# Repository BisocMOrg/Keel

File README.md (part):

# Keel

Keel is a Raspberry Pi 4 robot baseboard with two DC motor channels, an ultrasonic sensor interface, six RGB LEDs, four illuminated buttons and I²C expansion. The Pi mounts inverted through a 40-pin socket. A hardware AND gate enables the motors only when the host requests it, the STM32C011 controller grants permission and the fault bus is clear.

The repository contains the R3 hardware design, STM32 firmware, C libraries for board control (libkeel) and camera operation (libkeel-camera), Python and Java bindings, and a 3D-printable chassis.

The R3 board has been manufactured, assembled and tested on hardware. The [verification results](#verification)
cover motor drive, the safety chain, LEDs, buttons and camera operation.

<p align="center">
  <br>
  <sub>Robot chassis design (render).</sub>
</p>

## Contents

- [Hardware](#hardware)
- [Motor enable chain](#motor-enable-chain)
- [Software](#software)
- [Demonstrators](#demonstrators)
- [Camera](#camera)
- [Robot chassis](#robot-chassis)
- [Building and installing](#building-and-installing)
- [Verification](#verification)
- [Repository layout](#repository-layout)
- [Documentation](#documentation)
- [Licences](#licences)

## Hardware

| Parameter | Value |
|---|---|
| Revision | R3 (2026-11) |
| Board | 106 x 150 mm, 6 layers, 1.6 mm, KiCad 10 |
| Host | Raspberry Pi 4, mounted upside down on a 2x20 socket (PI1) with a booster header, about 19.5 mm stack height |
| Supply | 5 V from host header pins 2 and 4, through a TVS clamp (D7) and an eFuse (U2, TPS259474L) with under- and over-voltage cut-off; over-voltage trip 5.28-5.47 V |
| Motor driver | DRV8411 dual H-bridge (U1), four host PWM lines, current regulation through 0.82 Ohm sense resistors: 0.22-0.28 A per motor |
| Motor connectors | J2 (left), J3 (right): 2-pin 1.5 mm side entry |
| Safety controller | STM32C011F4P6 (U12) on its own 3.3 V rail (U16), window watchdog TPS3436 (U13), 3-input AND gates for the motor (U14) and servo (U27) enables |
| Ultrasonic socket | J1, 4-pin 2.54 mm (5 V, TRIG, ECHO, GND) for an HC-SR04; 5 V switched by U30 (TPS2553-1), 108-154 mA limit; open-drain trigger buffer and echo buffer |
| Servo header | J5, not fitted on R3; 5 V switched by U15 (TPS2553-1), 444-568 mA limit, timed bursts only |
| LEDs | Six RGB LEDs on the bottom side, IS31FL3218 driver (U3) at I2C address 0x54, up to 6.3 mA per channel; four white LEDs at the buttons on host GPIOs |
| Buttons | SW1-SW4 (A, B, X, Y), active low on host GPIOs |
| Expansion | I2C through a repeater (U6) and an over-voltage protector (U10): two 4-pin 1.0 mm sockets (X1, X3) on a 3.3 V accessory rail (U4, LT1763), plus six unfitted header positions (J4, JP1-JP5) |
| ESD | Clamp arrays at every external connector and the buttons |
| Test access | 28 bare pads on the bottom side on a 2.54 mm grid |
| Programming | SW5 (4-pole DIP): all ON = programming (host GPIO0/1/7 connect to the controller's SWD and reset), all OFF = normal operation |

<p align="center">
  <br>
  <sub>Physical R3 board (top row) and CAD renders (bottom row); top side left, bottom side right.</sub>
</p>

### Connections

| Device | Connects to | Path |
|---|---|---|
| Raspberry Pi 4 | PI1, through a 2x20 booster header | Keel takes its 5 V from the Pi's header pins 2 and 4 and uses the GPIO lines listed below |
| Two DC gearmotors | J2 (left), J3 (right) | U1, behind the motor enable gate |
| HC-SR04 ultrasonic sensor | J1, near the front | 5 V switched and current-limited by U30; TRIG and ECHO buffered to GPIO13 and GPIO25 |
| I2C accessories | X1, X3 (pin 1 GND, pin 2 3.3 V, pin 3 SDA, pin 4 SCL) | U6 repeater and U10 over-voltage protector on I2C1 |
| Raspberry Pi Camera Module 2 or 3 | The Pi's own camera connector, with a 15-way 1.0 mm flat cable | Not through Keel |
| Power source, 5 V / 3 A | The Pi's USB-C input (the chassis uses a USB-C power bank) | Not through Keel: the board and the motors run from the Pi's 5 V |

Keel has no connection to the Pi's camera and display connectors, USB, Ethernet or HDMI, or to GPIO14 and GPIO15
(UART).

### Host GPIO assignment

| BCM | Header pin | Signal | Direction (host) | Function |
|---|---|---|---|---|
| 2, 3 | 3, 5 | I2C_SDA, I2C_SCL | bidirectional | I2C1: LED driver and expansion bus |
| 4 | 7 | I2C_INT | input | Expansion interrupt (buffered, active low) |
| 8, 11 | 24, 23 | MOTOR_LP, MOTOR_LN | output | Left motor PWM |
| 10, 9 | 19, 21 | MOTOR_RP, MOTOR_RN | output | Right motor PWM |
| 26 | 37 | MOTOR_EN | output | Motor enable request (AND gate input; also the arming handshake) |
| 18 | 12 | HOST_HEARTBEAT | output | Heartbeat to the safety controller |
| 19 | 35 | SERVO_REQUEST | output | Servo power request |
| 12 | 32 | SERVO_SIG | output | Servo signal |
| 20 | 38 | HOST_FAULT | input | READY: high while the safety controller is healthy |
| 21 | 40 | HOST_ARMED | input | ARMED: high while the motor driver is enabled |
| 13 | 33 | US_TRIG | output | Ultrasonic trigger |
| 25 | 22 | US_ECHO | input | Ultrasonic echo |
| 5, 6, 16, 24 | 29, 31, 36, 18 | SW_A, SW_B, SW_X, SW_Y | input | Buttons, active low |
| 23, 22, 17, 27 | 16, 15, 11, 13 | LED_A, LED_B, LED_X, LED_Y | output | Button LEDs |
| 0, 1, 7 | 27, 28, 26 | PI_PROG_SWDIO, PI_PROG_SWCLK, PI_PROG_NRST | - | Controller programming, connected only while SW5 is ON |
| 14, 15 | 8, 10 | - | - | Not connected |

<p align="center">
  <br>
  <sub>Schematic sheet 1 of 11 (host socket and block diagram). The full schematic is <a href="hardware/schematic/Keel_R3_schematic.pdf">Keel_R3_schematic.pdf</a>.</sub>
</p>

## Motor enable chain

```mermaid
flowchart LR
    subgraph PI["Raspberry Pi 4"]
        LIB["libkeel control loop"]
    end
    LIB -- "HOST_HEARTBEAT (GPIO18)" --> MCU["STM32C011 (U12)"]
    WD["Window watchdog (U13)"] -. "reset on missed service" .-> MCU
    LIB -- "MOTOR_EN (GPIO26)" --> AND{"AND (U14)"}
    MCU -- "MCU_MOTOR_PERMIT" --> AND
    FB["MOTOR_FAULT bus (open drain)"] --> AND
    AND -- "MOTOR_EN_SAFE = nSLEEP" --> DRV["DRV8411 (U1)"]
    LIB -- "PWM, 4 lines" --> DRV
    DRV --> MOT(("J2, J3"))
    MCU -- "READY (GPIO20)" --> LIB
    AND -- "ARMED (GPIO21)" --> LIB
```

- `nSLEEP = MOTOR_EN AND MCU_MOTOR_PERMIT AND MOTOR_FAULT`. The servo switch enable is built the same way (U27) with
  the controller's servo permit.
- The controller raises `MCU_MOTOR_PERMIT` only after an arming sequence on `MOTOR_EN` with a heartbeat inside its
  timing window, and lowers it on a missed heartbeat, a PWM edge outside the permitted states, or any latched fault.
  After a fault the host must repeat the arming sequence.
- `MOTOR_FAULT` is an open-drain bus with a 22 kOhm pull-up. It is pulled low by the 5 V supervisor (U11, below
  4.65 V), the watchdog output (U13) and the sensor and servo switches (U30, U15). A low bus disables both enables and
  resets the controller. The controller cannot drive the bus.
- U1's own nFAULT output (pin 8) is not connected: on the bus it would gate U1's own nSLEEP during its wake-up pulse.
  The DRV8411 still protects itself (over-current, thermal shutdown, under-voltage lockout).
- The disable path contains no firmware: the host or the fault bus can remove motor power alone.

Measured on hardware: `ARMED` falls 9-37 us after a host stop command, and 51-71 ms after the host process is killed
(heartbeat stops; design bound about 86 ms after the last heartbeat edge). The full host and controller contract is in
[`firmware/safety-mcu/docs/mcu_integration.md`](firmware/safety-mcu/docs/mcu_integration.md).

The board is an engineering safety interlock, not a certified safety device.

## Software

| Component | Description |
|---|---|
| [`software/libkeel`](software/libkeel/README.md) | C11 host library for the board, ABI 1.0, `libkeel.so.1`, header `keel/keel.h`. Backends: `r3` (GPIO character device, i2c-dev, real-time PWM thread) and `simulator` (steps an unmodified copy of the controller's policy code). |
| [libkeel-camera](software/libkeel/docs/camera.md) | C camera library, ABI 1.0, `libkeel-camera.so.1`, header `keel/camera.h`, in the libkeel source tree (`software/libkeel/src/camera`). See [Camera](#camera). |
| Tools | `keel-doctor` (checks device access, GPIO lines, real-time limits, I2C), `keel-live` (hardware test modes), `keel-demo`, `keel-setup` (groups and boot configuration), all in `keel-tools`; `keel-camera` (camera list, stills, recording, streaming, raw frames) in its own package. |
| Debian packages | Board: `libkeel1`, `libkeel-dev`, `keel-common`, `keel-tools`. Camera: `libkeel-camera1`, `libkeel-camera-dev`, `keel-camera`. Python binding: `python3-keel`. The board packages do not depend on the camera packages. |
| [`software/bindings/python`](software/bindings/python/README.md) | Python 3.11+ binding over ctypes, distribution `keel-robot`, import name `keel`. Packages `keel.errors`, `keel.loop`, `keel.state`, `keel.peripherals`, `keel.sim`, and `keel.camera` for the camera; `keel` re-exports every board name. |
| [`software/bindings/java`](software/bindings/java/README.md) | Java 25+ binding over the Foreign Function and Memory API, `io.github.bisocmorg:keel`, module `io.github.bisocmorg.keel`. Packages `io.github.bisocmorg.keel` and its subpackages `errors`, `loop`, `state`, `peripherals`, `sim`, and `camera` for the camera; no native code. |
| [Java and Python demonstrators](software/demonstrator/README.md) | Two independent Pi servers with a shared local browser dashboard: interactive 3D robot, LEDs, hold-to-drive motors, ultrasonic ranging, camera streaming/photos and measured timing statistics. |
| [`firmware/safety-mcu`](firmware/safety-mcu/README.md) | STM32C011 firmware, release image (`release/safety_controller.hex`, SHA-256 `1608d866...`) and the programming tool for the Pi (`programming/flash_safety_mcu.sh`). |

The low-level bindings pass calls through to libkeel. Their sequential task layer schedules bounded actions
without replacing the native safety policy. Constants and structure layouts are generated from `keel.h` and
`camera.h` and checked in CI.

Threading rule: the thread that runs the control loop owns the device. Motion calls from any other thread are refused
(`KEEL_E_CONFLICT`); stop calls (`keel_disarm`, `keel_emergency_stop`, `keel_close`) are accepted from any thread. The
GPIO lines are requested exclusively, so a second process cannot open the board (`KEEL_E_IN_USE`).

Sequential task (Python): drive both motors at 20% for 3 s, pause with motor drive off, then make a timed left turn.
The task runner handles arming, the hardware loop, bounded movement and cleanup. Students write their own
behaviours; see the [Java/Python task guide](software/bindings/docs/tasks.md).

```python
import time

import keel
from keel.task import KeelTask

class FirstTask(KeelTask):
    """Run a short sequence of bounded robot movements."""

    def run(self) -> None:
        """Drive, pause with motor drive off, then turn."""
        self.keel.drive_for(20, 20, 3000)  # percent left/right, milliseconds
        time.sleep(0.5)
        self.keel.turn_left_for(600)

keel.run(FirstTask())
```

<details>
<summary>Java</summary>

```java
import io.github.bisocmorg.keel.Keel;
import io.github.bisocmorg.keel.task.KeelTask;

public final class FirstTask extends KeelTask {
    /**
     * Runs sequential actions, each ending with zero motor drive.
     * @throws Exception if an action fails or the task is interrupted
     */
    @Override
    protected void run() throws Exception {
        keel.driveFor(20, 20, 3000);
        Thread.sleep(500);
        keel.turnLeftFor(600);
    }

    /**
     * Executes this task and closes its hardware resources.
     * @param args unused command-line arguments
     * @throws Exception if opening the robot or running the task fails
     */
    public static void main(String[] args) throws Exception {
        Keel.run(new FirstTask());
    }
}
```

`java --enable-native-access=ALL-UNNAMED -cp keel-1.0.0.jar FirstTask.java`

</details>

<details>
<summary>C</summary>

```c
#include <keel/keel.h>
#include <stdio.h>

int main(void)
{
    keel_open_report report = {.struct_size = sizeof report};
    keel_device *dev = NULL;
    int32_t rc = keel_open(NULL, &dev, &report);
    if (rc != KEEL_OK) {
        fprintf(stderr, "keel_open: %s: %s\n", keel_status_name(rc), report.hint);
        return 1;
    }

    keel_cycle_input in = {.struct_size = sizeof in, .health = KEEL_HEALTH_ALL};
    keel_snapshot out = {.struct_size = sizeof out};
    uint64_t next = 0;
    keel_now_us(dev, &next);
    rc = keel_request_arm(dev);

    for (int i = 0; rc == KEEL_OK && i < 300; ++i) {
        in.cycle_id++;
        if (out.state == KEEL_STATE_ARMED) {
            in.command = KEEL_CYCLE_DRIVE;
            in.left = 200;
            in.right = 200;
        }
        rc = keel_cycle(dev, &in, &out);
        next += 10000;
        if (rc == KEEL_OK) {
            rc = keel_sleep_until(dev, next);
        }
    }
    keel_close(dev, NULL);
    return rc == KEEL_OK ? 0 : 1;
}
```

`cc -std=c11 drive.c $(pkg-config --cflags --libs keel) -o drive`

</details>

Further examples are in [`software/bindings/python/examples`](software/bindings/python/examples) and
[`software/bindings/java/examples`](software/bindings/java/examples): buttons, LEDs, ranging, fault handling and
driving, and for the camera frames, streaming and stills.

The board examples use sequential tasks or managed `RobotSession` connections instead of constructing
hardware control loops. The browser demonstrators use managed sessions with explicit arming and finite
drive-command leases. Camera-only examples keep the high-level camera API and need no board connection.

## Demonstrators

The [Java and Python demonstrators](software/demonstrator/README.md) run on the Raspberry Pi and serve a browser
dashboard over the local network. They are independent server implementations with the same controls and shared
browser interface. Each uses its own language binding to `libkeel` and `libkeel-camera`; the browser assets and 3D
model are bundled, so the dashboard needs no internet connection.

<p align="center">
  <br>
  <sub>Shared Java/Python dashboard, shown with Python connected to the robot and motors disarmed.</sub>
</p>

| Implementation | Source | Default browser address |
|---|---|---|
| Python 3.11+ | [`software/demonstrator/python/`](software/demonstrator/python/) | `http://ROBOT:8787` |
| Java 25+ | [`software/demonstrator/java/`](software/demonstrator/java/) | `http://ROBOT:8788` |

Replace `ROBOT` with the Pi's hostname or IP address. Both provide:

- An interactive 3D model of the assembled robot, with selectable wheels, LEDs, buttons, camera and ultrasonic sensor.
- Individual RGB LEDs and button indicators, physical button readings and ultrasonic distance measurements.
- Motor arming, hold-to-drive controls, disarming and a latched emergency stop. Wheel animation shows commanded
  duty, not measured speed.
- A 640 x 480 MJPEG camera feed, full-resolution JPEG photos and autofocus on supported cameras. Taking a photo
  briefly pauses and resumes the stream.
- Network round-trip time, estimated camera-frame age with clock-sync uncertainty, delivered FPS, throughput,
  dropped/skipped frames, control-loop timing and CPU temperature when available.

Follow the [build and upload instructions](software/demonstrator/README.md#build-on-the-pc) to package both versions
and copy them to the Pi. From the extracted deployment directory:

```sh
./demo use python   # Python controls the hardware; Java runs in mock mode
./demo token        # Access token to enter in the browser
./demo use java     # Switch hardware control to Java; Python becomes mock
./demo mock         # Run both without physical hardware
./demo stop         # Stop both servers
```

Only one implementation can own the physical board and camera at a time. The browser requires explicit control
ownership and motor arming. Motor commands expire after 350 ms without a fresh drive request, and controller
ownership expires after 1.5 s without a heartbeat. The native safety controller remains active in hardware mode.

The [demonstrator guide](software/demonstrator/README.md) covers direct launch, deployment, tests and the meaning of
the timing statistics; [API.md](software/demonstrator/API.md) describes the shared HTTP protocol.

## Camera

The robot's camera is a Raspberry Pi Camera Module 2 or Camera Module 3 on the Pi's own camera connector.
libkeel-camera drives it through libcamera and the Pi's hardware encoders:

- raw frames for a program, in I420, RGB888 or BGR888, converted by the Pi's image signal processor;
- H.264 and MJPEG from the hardware encoders, read by the program or written by the library to files, TCP
  connections, a listening TCP port for several viewers, UDP or standard output;
- JPEG stills up to the full sensor resolution;
- autofocus on Camera Module 3.

Dependencies:

- libkeel has no camera code and no camera dependency.
- libkeel-camera needs libcamera (with its Raspberry Pi IPA module) and the kernel's V4L2 devices, and starts no other
  programs. Two optional build features: libjpeg for stills larger than 1920x1920, and FFmpeg's libavformat for
  `.mp4`, `.mkv`, `.mov` and `.ts` files and `rtsp://`, `rtmp://` and `srt://` streams. The release packages are
  built with libjpeg and without libavformat.
- The camera library needs neither libkeel nor the board, and libkeel works without the camera library.
- On another operating system or a minimal image (Yocto, for example), the image needs the camera enabled in
  `config.txt` (`camera_auto_detect=1`, or `dtoverlay=imx219` or `dtoverlay=imx708`), the Raspberry Pi camera and
  codec drivers and libcamera with its Raspberry Pi pipeline: camera.md section 1 lists them.

From the command line, on the robot:

```sh
keel-camera list                                                # cameras and sensor modes
keel-camera still -o photo.jpg                                  # full-resolution JPEG
keel-camera stream 'tcp://:5000?listen'                         # H.264 for viewers on port 5000
keel-camera frames --format bgr888 -W 320 -H 240 | python3 model.py   # raw frames into a program
```

On another computer, `ffplay -f h264 -fflags nobuffer tcp://ROBOT:5000` or OpenCV's
`cv2.VideoCapture("tcp://ROBOT:5000", cv2.CAP_FFMPEG)` shows the stream.

From Python: frames into code while the library serves the video on port 5000.

```python
from keel import camera

with camera.open(width=640, height=480, pixel_format=camera.PixelFormat.BGR888) as cam:
    cam.set_encoder(camera.Codec.H264)
    cam.start_output("tcp://:5000?listen")
    cam.start()
    for count, frame in enumerate(cam.frames(), start=1):
        image = frame.array()  # numpy (480, 640, 3), B, G, R: a view of the frame, no copy
        print(frame.sequence, frame.timestamp_ns, image.mean())
        if count == 300:  # ten seconds at 30 fps
            break
```

`frame.array()` needs numpy (`sudo apt install python3-numpy`); `frame.data` and `frame.to_bytes()` work
without it.

The Java API in `io.github.bisocmorg.keel.camera` has the same names and shapes (`Camera.open`, `frames()`,
`setEncoder`, `startOutput`, `captureStill`), with frames as direct buffers, `MemorySegment`s or `BufferedImage`s.
The camera guide, [`software/libkeel/docs/camera.md`](software/libkeel/docs/camera.md), covers connecting the camera,
the tool, viewers and OpenCV on another computer, recording, stills, frames into a model, and the C, Python and Java
APIs.

## Robot chassis

A 3D-printed chassis turns the board into a two-wheeled robot. The Keel board is the base plate, with the Raspberry
Pi 4 upside down on top. Two micro gearmotors and a ball caster sit underneath. An HC-SR04 ultrasonic sensor plugs
into J1 at the front, a Raspberry Pi Camera Module 2 or 3 sits on a tilting mast, and a USB-C power bank sits on the
top plate. The printed parts are 17 PETG pieces, about 3.2 h of printing, fastened with M2 and M2.5 screws, nuts and
standoffs.

| Topic | Location |
|---|---|
| Printed parts, print settings, purchased parts, fasteners, power-bank sizes, fit notes | [`chassis/README.md`](chassis/README.md) |
| Step-by-step build guide | [`chassis/assembly.md`](chassis/assembly.md) |
| Print files: one 3MF per part, or four plates for 350 x 320 mm beds | [`chassis/print/parts/`](chassis/print/parts), [`chassis/print/plates/`](chassis/print/plates) |
| Assembled robot, one named object per part | [`chassis/Keel_R3_robot_assembly.3mf`](chassis/Keel_R3_robot_assembly.3mf) |

The 3MF files are in millimetres and carry no printer or filament profile. Order of work: the board assembled,
brought up and its safety controller programmed ([Building and installing](#building-and-installing)), a microSD
card with the robot's operating system, the printed and purchased parts, the build guide, then the host software.

## Building and installing

**Board.** Gerber and drill files, IPC-D-356 netlist and fabrication drawing:
[`hardware/fabrication/Keel_R3_Gerbers_Drill.zip`](hardware/fabrication/Keel_R3_Gerbers_Drill.zip). BOM, placement
file and assembly drawing: [`hardware/assembly`](hardware/assembly). Stack-up and fabrication notes:
[`hardware/README.md`](hardware/README.md). Bring-up procedure and expected readings:
[`hardware/docs/bringup.md`](hardware/docs/bringup.md).

**Safety controller.** Set SW5 to ON, program the release image from the Pi with
`programming/flash_safety_mcu.sh`, set SW5 to OFF. See [`firmware/safety-mcu/README.md`](firmware/safety-mcu/README.md).

**Host software** (Raspberry Pi 4 with the robot's operating system, 64-bit Ubuntu 26.10 for Raspberry Pi, written
to its microSD card with Raspberry Pi Imager, for example; other distributions build the packages themselves, see
`deploy.md`):

```sh
curl -fsSL https://github.com/BisocMOrg/Keel/releases/latest/download/install.sh | sudo sh -s -- --user "$USER" --python
sudo reboot
keel-doctor
```

`install.sh` verifies the downloads against the release's `SHA256SUMS`, installs the board packages (`libkeel1`,
`keel-common`, `keel-tools`) and the camera packages (`libkeel-camera1`, `keel-camera`; apt adds libcamera from the
distribution) and runs `keel-setup` (device groups, including `video` for the camera; SPI0 off, I2C1 on). Where
the system cannot provide the camera packages' libcamera, it installs the board packages alone and says so.
Options: `--dev` (headers, CMake package, pkg-config files), `--python` (Python binding), `--no-camera`,
`--version X.Y.Z`, `--i2c-fast`, `--dry-run`. Java requires `openjdk-25-jre-headless` and the release jar. Manual
installation and service setup: [`software/libkeel/docs/deploy.md`](software/libkeel/docs/deploy.md).

**From source** (libkeel, any Linux; C11 compiler, CMake 3.21+; for the camera library also a C++17 compiler and
`libcamera-dev`, optionally `libjpeg-dev`):

```sh
cd software/libkeel
cmake --preset release && cmake --build --preset release && ctest --preset release
```

Presets: `dev`, `release`, `asan-ubsan`, `tsan`, `sim-only`, `cross-arm64`. The camera library is built when
libcamera is found (`-DKEEL_CAMERA=ON` requires it, `OFF` leaves it out). For development without a board, build
`sim-only` and set `KEEL_LIBRARY=$PWD/build/sim-only/libkeel.so.1` and `KEEL_BACKEND=simulator`; the bindings and
examples then run against the simulator. Builds from the presets also contain a synthetic test camera, selected with
`KEEL_CAMERA_TEST_SOURCE=1` (camera.md section 6).

## Verification

Hardware tests on an R3 board with the release firmware and libkeel 1.0, 2026-11-07 to 2026-11-09:

| Test | Result |
|---|---|
| Motor drive | Both motors, both directions, each motor individually; from C (`keel-live`), Python and Java |
| Safety chain (`keel-live --safety`) | 17/17 pass: stop to ARMED low 9-37 us; heartbeat loss removes motor power; re-arm hold-off 1 s; emergency stop latches |
| Host process killed during drive | ARMED low after 51-71 ms (3 runs) |
| PWM timing, 600 s under build load | 99.9th-percentile wake lateness 216 us, maximum 369 us, no overruns |
| LEDs and buttons | All RGB channels and button LEDs checked visually; buttons read |
| Installation | Debian packages built on the robot (arm64 test suite 188/188), installed with `install.sh`; `keel-doctor` 13 checks passed, 1 skipped (the firmware's throttling flags are unavailable), 0 failed |
| Python and Java bindings | Non-motion hardware test suites 7/7 each; motion examples arm, drive and stop |
| Camera (Camera Module 2) | `keel-camera`: listing, stills up to 3280x2464, H.264 up to 1920x1080 and MJPEG recording, raw frames, streams to a listening TCP port, UDP and standard output, decoded with FFmpeg and OpenCV on another computer; Python and Java camera hardware suites 8/8 each |
| Firmware | Release image rebuilds byte-identically on Linux and Windows; 2,832,503 unit-test assertions pass |

Not yet characterised: ultrasonic ranging on hardware, the servo path (J5 not fitted), long-term thermal, ESD and EMC
behaviour, Camera Module 3 on hardware (its autofocus is tested on the synthetic camera only), and the chassis as a
printed and assembled robot (its fit relies on the purchased-part dimensions in the
[fit notes](chassis/README.md#fit-notes)). Test plans: [`hardware/docs/bringup.md`](hardware/docs/bringup.md),
[`firmware/safety-mcu/docs/qualification.md`](firmware/safety-mcu/docs/qualification.md).

## Repository layout

| Path | Contents |
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
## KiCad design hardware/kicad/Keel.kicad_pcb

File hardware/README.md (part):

# Keel hardware

Keel is a robot baseboard for a Raspberry Pi 4. The Pi plugs in upside down on top of it. Keel drives two DC motors and
powers an ultrasonic sensor. It has six RGB underlights, four buttons with LEDs, I2C expansion and a servo header
(J5, not fitted).

A small safety microcontroller and hardware logic gates decide when the motors and the servo get power. The Pi asks
for power; it cannot force it on. A fault, a missed heartbeat or a stuck safety MCU removes it.

- Revision: **R3** (2026-11).
- Board: 106 x 150 mm, 6 layers, 1.6 mm.
- Design tool: KiCad 10.
- Copyright (c) 2026 BisocM. Licence: CERN-OHL-P-2.0 (see [Licence](#licence)).

Related folders:
- `hardware/kicad/`: the KiCad project.
- `hardware/fabrication/`, `hardware/assembly/`, `hardware/3d/`: the production outputs.
- `hardware/schematic/`: the schematic as a PDF, and sheet 1 as an image.
- `hardware/renders/`: rendered views of the board.
- `hardware/docs/`: bring-up, test pads and design notes.
- `firmware/`: the safety MCU firmware and the Pi flashing tool.
- `software/`: the host software for the Pi.
- `chassis/`: the 3D-printed robot chassis that uses the board as its base plate.

## Blocks

| Block | Main parts | What it does |
|---|---|---|
| Pi 4 interface | PI1 (2x20 socket, Samtec SSW-120-01-G-D); U29, U28, U8, U9 buffers | The Pi 4 mounts upside down on a booster header in PI1. The board takes its 5 V from Pi header pins 2 and 4. Pi signals reach the safety MCU through buffer U29. U28 returns READY and ARMED to the Pi. U8 and U9 buffer the ultrasonic, servo-signal and expansion-interrupt lines. |
| Power entry | D7 TVS, U2 eFuse (TPS259474L), U11 supervisor | U2 switches PI_5V to SYS_5V, with under- and over-voltage cut-off (over-voltage trip 5.28-5.47 V). U11 pulls the fault bus low if SYS_5V drops below 4.65 V. |
| Rails | U16 (TPS70933), U4 (LT1763-3.3), D5, C4, D6 | U16 makes SAFE_3V3 for the safety domain. U4 makes EXP_3V3 for expansion. The motor rail VM_MOTOR comes from SYS_5V through Schottky D5, with 47 uF (C4) and a TVS (D6). |
| Motor driver | U1 DRV8411 (dual H-bridge), R35/R36 0.82 Ohm shunts, J2/J3 | Drives the left (J2) and right (J3) motors from four Pi PWM lines. Current regulation limits each motor to 0.22-0.28 A. U1 sleeps unless the safety gate holds nSLEEP high. |
| Safety gate | U14, U27 (3-input AND gates), fault bus | Motor power: nSLEEP = Pi MOTOR_EN (GPIO26) AND MCU motor permit AND fault bus high. Servo power uses the same rule with the MCU servo permit. Pull-downs hold MOTOR_EN and both permits low by default. |
| Safety MCU | U12 STM32C011F4P6, U13 TPS3436 window watchdog, SW5 | U12 checks the Pi heartbeat, the arming handshake, the PWM inputs and the servo request, then grants the permits. U13 resets it and pulls the fault bus low if it stops kicking the watchdog. SW5 selects RUN or PROG. |
| Fault bus | MOTOR_FAULT (open drain, 22k pull-up) | Driven low by U11, U13, U15 and U30. A low bus turns off both gates at once and resets U12. U12 cannot drive it. |
| Servo and sensor power | U15, U30 (TPS2553-1 switches), J5, J1 | U15 feeds SERVO_5V (J5, 444-568 mA limit, short timed bursts only). U30 feeds SENSOR_5V (J1, 108-154 mA limit). Both latch off on overload and pull the fault bus low. |
| Lighting | U3 IS31FL3218 (I2C 0x54), RGB1-RGB6, D1-D4 | Six RGB LEDs on the underside, driven by U3 at up to 6.34 mA per channel. Four white button LEDs on Pi GPIOs. |
| Buttons | SW1-SW4 | Four push buttons (A, B, X, Y), active low on Pi GPIOs. |
| Expansion | U6, U7 (TCA9517A), U10 (TPD2S703-Q1), X1, X3, J4, JP1-JP5 | The Pi I2C bus reaches the LED driver through U7 and the expansion connectors through U6 and the over-voltage protector U10. X1/X3 (silk "I2C") are 4-pin JST-SH I2C sockets: pin 1 GND, pin 2 EXP_3V3, pin 3 SDA, pin 4 SCL. J4 (1x5) and JP1-JP5 (2x5 header positions, silk "EXP") are not fitted. |
| ESD | U17-U26 (TPD4E05U06), D8-D11 (TPD1E05U06), D6, D7 | Clamp arrays sit at the expansion connectors (X1, X3, J4, JP1-JP5), the sensor socket J1 and the servo header J5. D8-D11 protect the button lines. D7 and D6 are TVS diodes on the 5 V input and the motor rail. |
| Test pads | TP1-TP47 (28 pads) | Bare pads on the underside, in six labelled rows on a 2.54 mm grid. See `hardware/docs/test_points.md`. |

Programming: SW5 is a 4-pole DIP switch, marked "ON = PROG / OFF = RUN". At PROG, Pi GPIO0, GPIO1 and GPIO7 connect
to the MCU's SWD and reset pins, the watchdog is disabled and both permits are clamped low. The MCU is programmed from
the Pi with the tool in `firmware/`. RUN (all OFF) is the only operating state.

The rationale behind these choices is in `hardware/docs/design_notes.md`.

## Design note: U1 nFAULT is not connected

U1 (DRV8411) pin 8, nFAULT, is intentionally left unconnected. It has a no-connect flag in the schematic, and pad 8
has no track.

Why: the fault bus MOTOR_FAULT is an input of the safety gate U14, and U14 drives U1's own nSLEEP (MOTOR_EN_SAFE).
The DRV8411 pulls nFAULT LOW briefly each time it wakes from sleep. On the fault bus, that pulse would drop U1's own
nSLEEP: the driver would go back to sleep, release nFAULT, be woken again by U14 and repeat. It would never stay
awake, and the motors would never arm. The design rule is that a part's fault output never gates that part's own
enable.

The driver still protects itself: it retries after an over-current, shuts down when too hot and locks out on
under-voltage.

Consequences for fault reporting:
- U1's over-current, over-temperature and under-voltage faults do not reach the fault bus. They do not turn off the
  gates or reset the safety MCU, and the host is not told about them.
- TP10 (MOTOR_FAULT) stays HIGH while U1 regulates its current or retries after an over-current
  (`hardware/docs/bringup.md`, section 5.4).
- Every other fault source still drives the bus: U11 (SYS_5V under-voltage), U13 (watchdog), and U15 and U30
  (switch over-current).
- To report U1 faults, a later revision can route nFAULT to its own MCU input and ignore it during the wake time.

## Opening the project

1. Install KiCad 10.
2. Open `hardware/kicad/Keel.kicad_pro`.

The project brings its own libraries through its local tables:
- symbols: `Keel.kicad_sym`;
- footprints: `Keel.pretty`;
- 3D models: `Keel.3dshapes`, referenced as `${KIPRJMOD}/Keel.3dshapes/...`.

The six fiducials use KiCad's standard `Fiducial` library. All footprints are also stored in the board file, so the
board opens without any external library.

Files:
- `Keel.kicad_sch`: the root schematic. Ten sheets: power, motor, motor_safety, interfaces, user_io, lighting,
  expansion, esd, testpoints and ground_probes.
- `Keel.kicad_pcb`: the board, with zones filled.
- `Keel.kicad_dru`: the custom design rules. They run as part of DRC.

The fabrication notes are on the board's User.Drawings layer.

Checks on the project (KiCad 10.0.6): DRC 0 errors and 0 warnings, 0 unconnected items, schematic parity 0, ERC 0.

## Production files

| Folder | File | Use |
|---|---|---|
| `hardware/fabrication/` | `Keel_R3_Gerbers_Drill.zip` | The bare-board upload and the fabrication reference. Gerbers (6 copper, 2 mask, 2 silk, 2 paste, outline), PTH and NPTH Excellon with drill maps, the job file, `drill_report.txt` (hole counts per tool), the IPC-D-356 netlist `Keel.ipc` for the electrical test, and `Keel_R3_fabrication_drawing.pdf` (fabrication notes, stack-up, outline and NO TAB edges). |
| `hardware/assembly/` | `Keel_R3_BOM.csv` | The assembly BOM: 61 lines, 140 placements. Quantities are per board. Every line has a manufacturer part number; approved alternates are listed where they exist. |
| | `Keel_R3_CPL.csv` | Centroid file: 138 SMD parts, both sides, Gerber coordinates. |
| | `Keel_R3_assembly_drawing.pdf` | Assembly drawing, A3, scale 3:2. Sheet 1: top side. Sheet 2: bottom side, viewed from below. Reference designators, pin 1 and polarity marks, unfitted positions crossed out, assembly notes. |
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
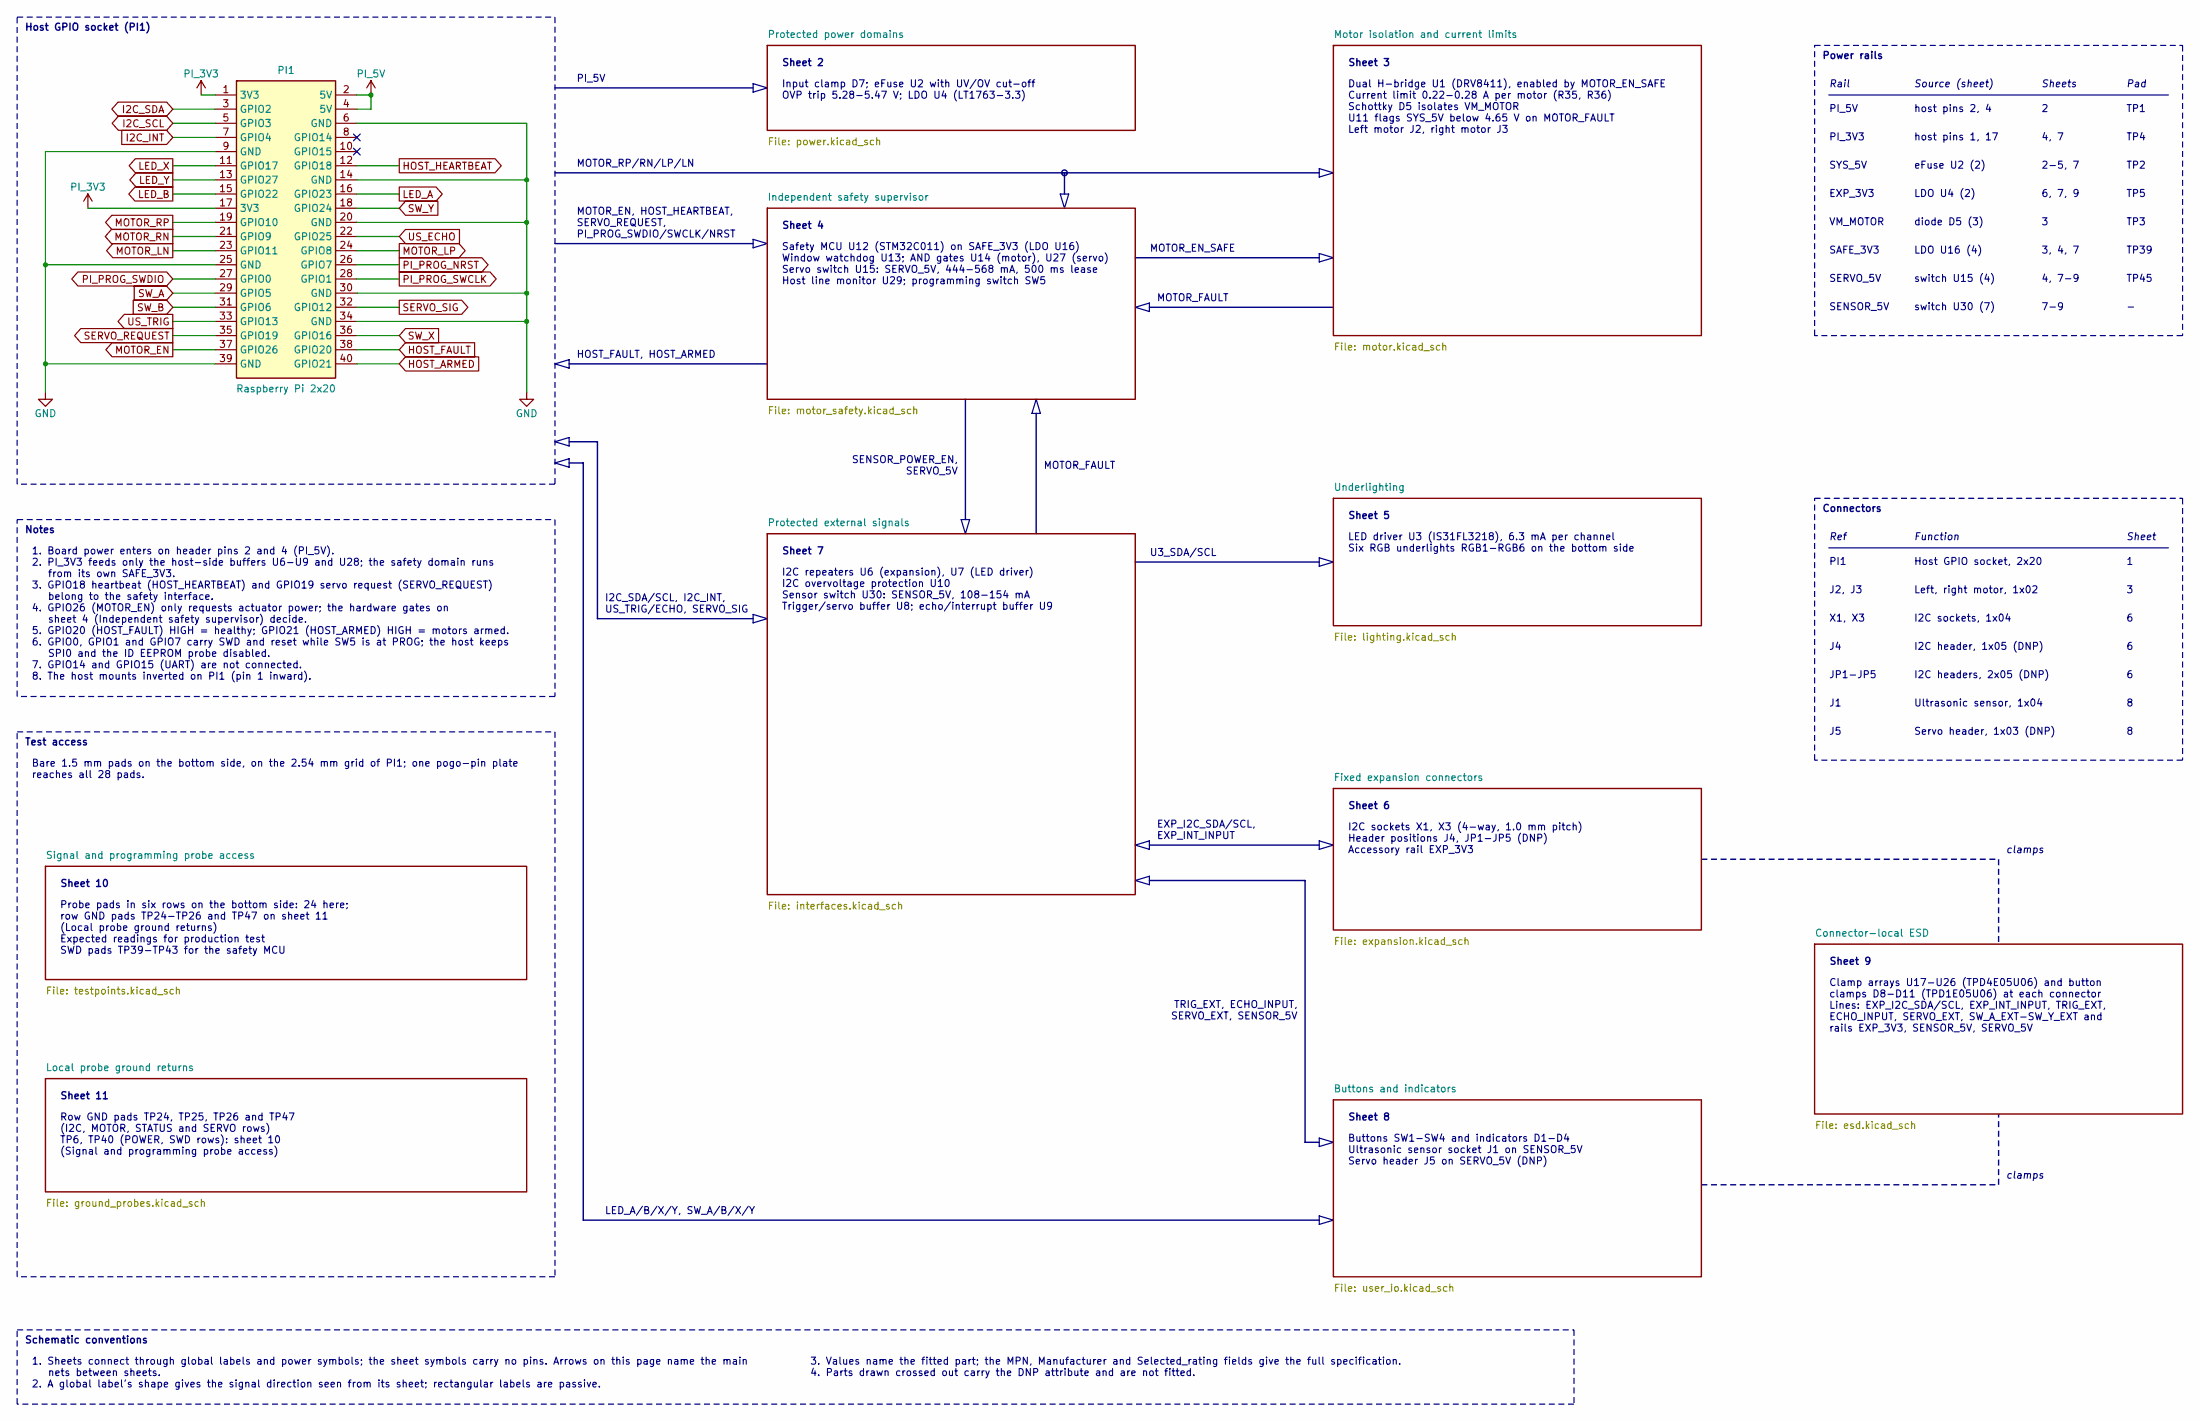
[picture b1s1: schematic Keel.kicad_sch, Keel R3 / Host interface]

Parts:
PI1: Raspberry Pi 2x20; PinSocket_2x20_P2.54mm_Vertical; MPN SSW-120-01-G-D

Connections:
GND: PI1.6 (GND), PI1.9 (GND), PI1.14 (GND), PI1.20 (GND), PI1.25 (GND), PI1.30 (GND), PI1.34 (GND), PI1.39 (GND); also elsewhere on the board
HOST_ARMED: PI1.40 (GPIO21); also elsewhere on the board
HOST_FAULT: PI1.38 (GPIO20); also elsewhere on the board
HOST_HEARTBEAT: PI1.12 (GPIO18); also elsewhere on the board
I2C_INT: PI1.7 (GPIO4); also elsewhere on the board
I2C_SCL: PI1.5 (GPIO3); also elsewhere on the board
I2C_SDA: PI1.3 (GPIO2); also elsewhere on the board
LED_A: PI1.16 (GPIO23); also elsewhere on the board
LED_B: PI1.15 (GPIO22); also elsewhere on the board
LED_X: PI1.11 (GPIO17); also elsewhere on the board
LED_Y: PI1.13 (GPIO27); also elsewhere on the board
MOTOR_EN: PI1.37 (GPIO26); also elsewhere on the board
MOTOR_LN: PI1.23 (GPIO11); also elsewhere on the board
MOTOR_LP: PI1.24 (GPIO8); also elsewhere on the board
MOTOR_RN: PI1.21 (GPIO9); also elsewhere on the board
MOTOR_RP: PI1.19 (GPIO10); also elsewhere on the board
PI_3V3: PI1.1 (3V3), PI1.17 (3V3); also elsewhere on the board
PI_5V: PI1.2 (5V), PI1.4 (5V); also elsewhere on the board
PI_PROG_NRST: PI1.26 (GPIO7); also elsewhere on the board
PI_PROG_SWCLK: PI1.28 (GPIO1); also elsewhere on the board
PI_PROG_SWDIO: PI1.27 (GPIO0); also elsewhere on the board
SERVO_REQUEST: PI1.35 (GPIO19); also elsewhere on the board
SERVO_SIG: PI1.32 (GPIO12); also elsewhere on the board
SW_A: PI1.29 (GPIO5); also elsewhere on the board
SW_B: PI1.31 (GPIO6); also elsewhere on the board
SW_X: PI1.36 (GPIO16); also elsewhere on the board
SW_Y: PI1.18 (GPIO24); also elsewhere on the board
US_ECHO: PI1.22 (GPIO25); also elsewhere on the board
US_TRIG: PI1.33 (GPIO13); also elsewhere on the board

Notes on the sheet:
Host GPIO socket (PI1)
Notes
1. Board power enters on header pins 2 and 4 (PI_5V). 2. PI_3V3 feeds only the host-side buffers U6-U9 and U28; the safety domain runs from its own SAFE_3V3. 3. GPIO18 heartbeat (HOST_HEARTBEAT) and GPIO19 servo request (SERVO_REQUEST) belong to the safety interface. 4. GPIO26 (MOTOR_EN) only reque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
Sheet 2
Input clamp D7; eFuse U2 with UV/OV cut-off OVP trip 5.28-5.47 V; LDO U4 (LT1763-3.3)
Sheet 4
Safety MCU U12 (STM32C011) on SAFE_3V3 (LDO U16) Window watchdog U13; AND gates U14 (motor), U27 (servo) Servo switch U15: SERVO_5V, 444-568 mA, 500 ms lease Host line monitor U29; programming switch SW5
Sheet 7
I2C repeaters U6 (expansion), U7 (LED driver) I2C overvoltage protection U10 Sensor switch U30: SENSOR_5V, 108-154 mA Trigger/servo buffer U8; echo/interrupt buffer U9
Sheet 3
Dual H-bridge U1 (DRV8411), enabled by MOTOR_EN_SAFE Current limit 0.22-0.28 A per motor (R35, R36) Schottky D5 isolates VM_MOTOR U11 flags SYS_5V below 4.65 V on MOTOR_FAULT Left motor J2, right motor J3
Sheet 5
LED driver U3 (IS31FL3218), 6.3 mA per channel Six RGB underlights RGB1-RGB6 on the bottom side
Sheet 6
I2C sockets X1, X3 (4-way, 1.0 mm pitch) Header positions J4, JP1-JP5 (DNP) Accessory rail EXP_3V3
Sheet 8
Buttons SW1-SW4 and indicators D1-D4 Ultrasonic sensor socket J1 on SENSOR_5V Servo header J5 on SERVO_5V (DNP)
Sheet 9
Clamp arrays U17-U26 (TPD4E05U06) and button clamps D8-D11 (TPD1E05U06) at each connector Lines: EXP_I2C_SDA/SCL, EXP_INT_INPUT, TRIG_EXT, ECHO_INPUT, SERVO_EXT, SW_A_EXT-SW_Y_EXT and rails EXP_3V3, SENSOR_5V, SERVO_5V
Sheet 10
Probe pads in six rows on the bottom side: 24 here; row GND pads TP24-TP26 and TP47 on sheet 11 (Local probe ground returns) Expected readings for production test SWD pads TP39-TP43 for the safety MCU
Sheet 11
Row GND pads TP24, TP25, TP26 and TP47 (I2C, MOTOR, STATUS and SERVO rows) TP6, TP40 (POWER, SWD rows): sheet 10 (Signal and programming probe access)
Test access
Bare 1.5 mm pads on the bottom side, on the 2.54 mm grid of PI1; one pogo-pin plate reaches all 28 pads.
Power rails
Rail
Source (sheet)
Sheets
Pad
PI_5V
host pins 2, 4
TP1
PI_3V3
host pins 1, 17
4, 7
TP4
SYS_5V
eFuse U2 (2)
2-5, 7

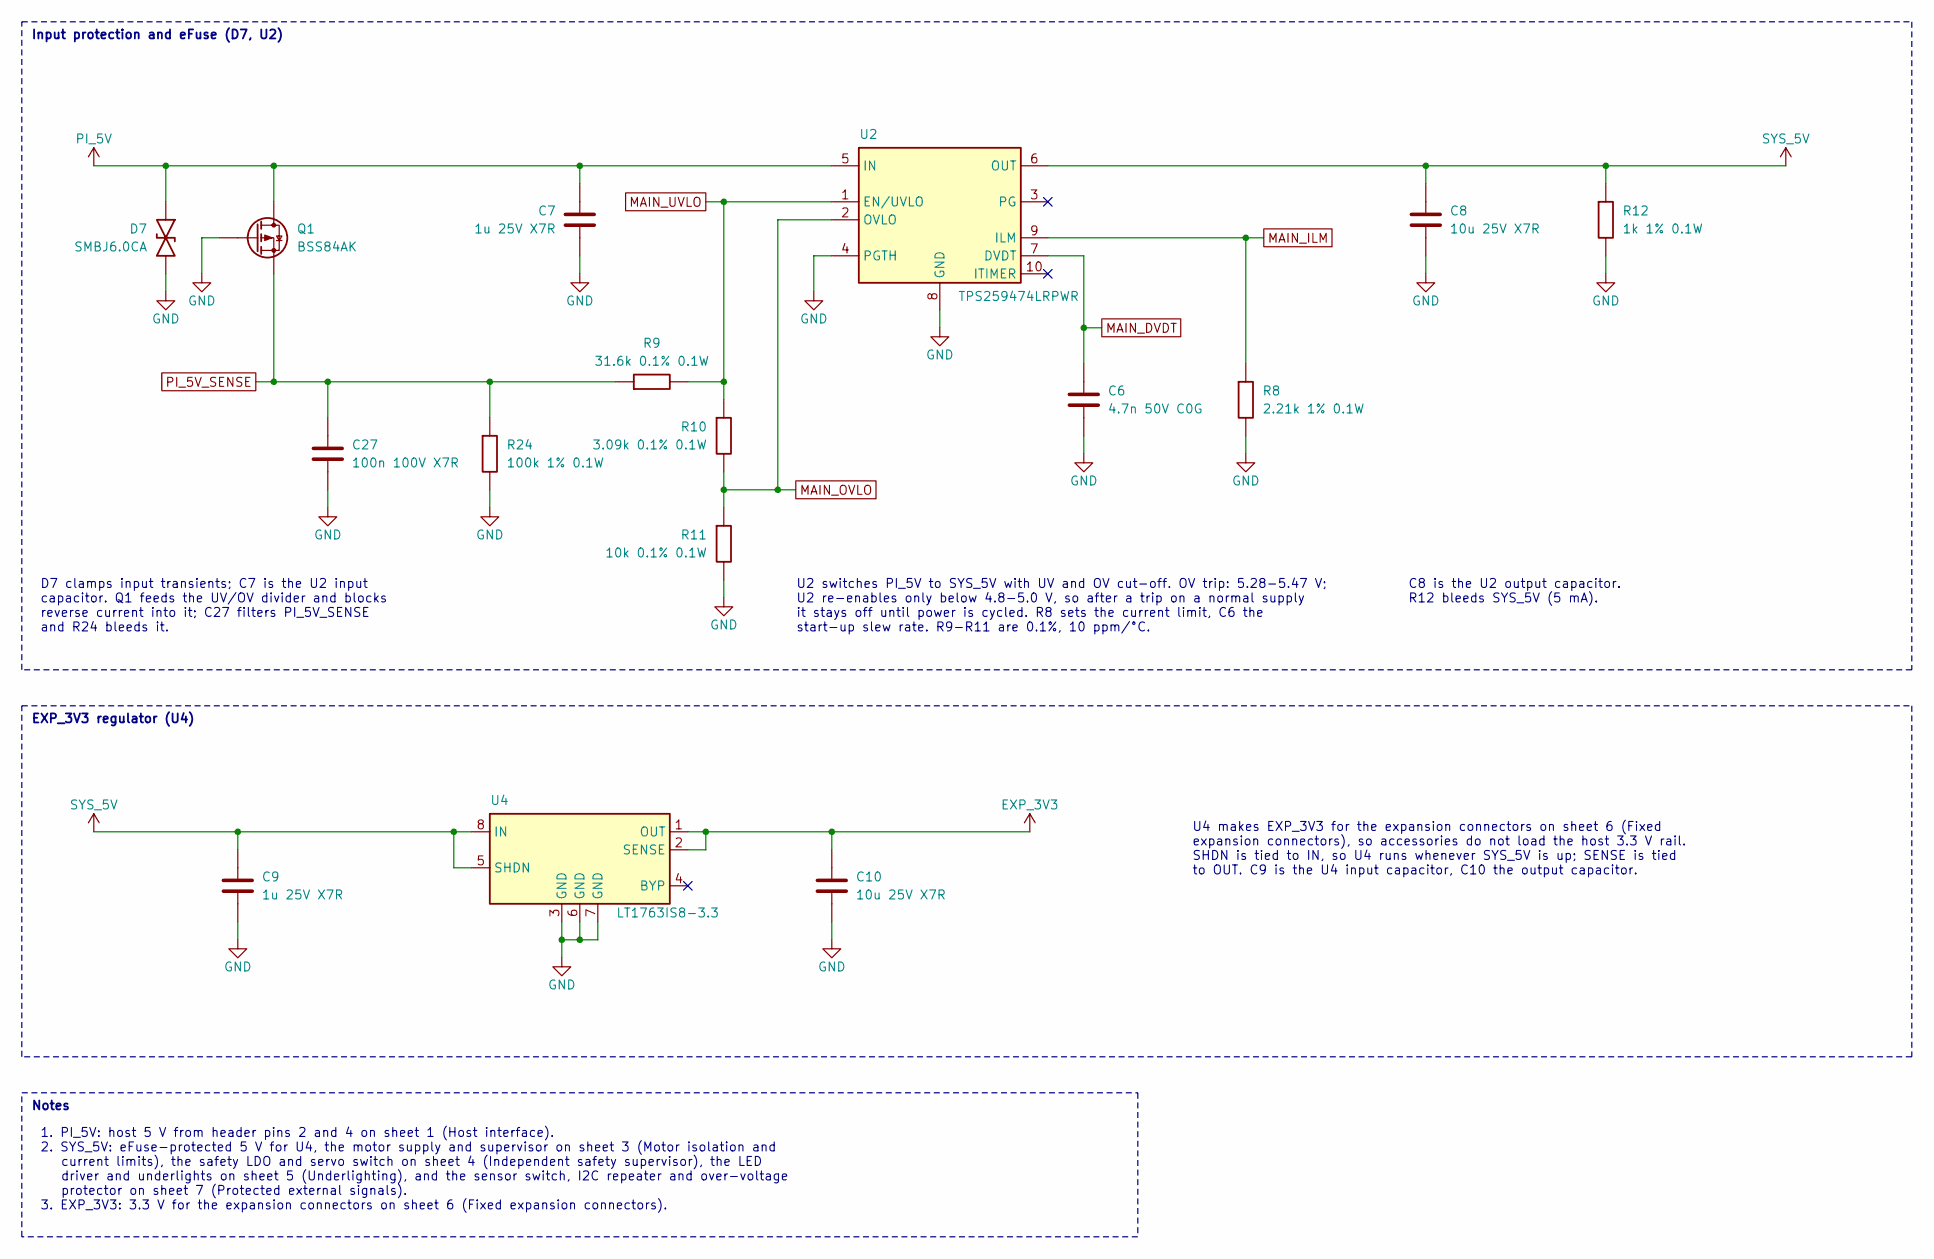
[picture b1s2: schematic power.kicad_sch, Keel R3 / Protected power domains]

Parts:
C6: 4.7n 50V C0G; C_0603_1608Metric; MPN GRM1885C1H472JA01D
C7, C9: 1u 25V X7R; C_0805_2012Metric; MPN GRM219R71E105KA88D
C8, C10: 10u 25V X7R; C_1206_3216Metric; MPN GRM31CR71E106KA12L
C27: 100n 100V X7R; C_0603_1608Metric; MPN GRM188R72A104KA35D
D7: SMBJ6.0CA; D_SMB; MPN SMBJ6.0CA
Q1: BSS84AK; SOT-23; MPN BSS84AK,215
R8: 2.21k 1% 0.1W; R_0603_1608Metric; MPN RC0603FR-072K21L
R9: 31.6k 0.1% 0.1W; R_0603_1608Metric; MPN ERA-3ARB3162V
R10: 3.09k 0.1% 0.1W; R_0603_1608Metric; MPN ERA-3ARB3091V
R11: 10k 0.1% 0.1W; R_0603_1608Metric; MPN RT0603BRB0710KL
R12: 1k 1% 0.1W; R_0603_1608Metric; MPN RC0603FR-071KL
R24: 100k 1% 0.1W; R_0603_1608Metric; MPN RC0603FR-07100KL
U2: TPS259474LRPWR; TPS25947_RPW0010A; MPN TPS259474LRPWR
U4: LT1763IS8-3.3; SOIC-8_3.9x4.9mm_P1.27mm; MPN LT1763IS8-3.3#PBF

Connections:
EXP_3V3: C10.1, U4.1 (OUT), U4.2 (SENSE); also elsewhere on the board
GND: C6.2, C7.2, C8.2, C9.2, C10.2, C27.2, D7.2, Q1.1, R8.2, R11.2, R12.2, R24.2, U2.4 (PGTH), U2.8 (GND), U4.3 (GND), U4.6 (GND), U4.7 (GND); also elsewhere on the board
MAIN_DVDT: C6.1, U2.7 (DVDT)
MAIN_ILM: R8.1, U2.9 (ILM)
MAIN_OVLO: R10.2, R11.1, U2.2 (OVLO)
MAIN_UVLO: R9.2, R10.1, U2.1 (EN/UVLO)
PI_5V: C7.1, D7.1, Q1.3, U2.5 (IN); also elsewhere on the board
PI_5V_SENSE: C27.1, Q1.2, R9.1, R24.1
SYS_5V: C8.1, C9.1, R12.1, U2.6 (OUT), U4.5 (SHDN), U4.8 (IN); also elsewhere on the board

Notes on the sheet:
Input protection and eFuse (D7, U2)
D7 clamps input transients; C7 is the U2 input capacitor. Q1 feeds the UV/OV divider and blocks reverse current into it; C27 filters PI_5V_SENSE and R24 bleeds it.
U2 switches PI_5V to SYS_5V with UV and OV cut-off. OV trip: 5.28-5.47 V; U2 re-enables only below 4.8-5.0 V, so after a trip on a normal supply it stays off until power is cycled. R8 sets the current limit, C6 the start-up slew rate. R9-R11 are 0.1%, 10 ppm/°C.
C8 is the U2 output capacitor. R12 bleeds SYS_5V (5 mA).
EXP_3V3 regulator (U4)
U4 makes EXP_3V3 for the expansion connectors on sheet 6 (Fixed expansion connectors), so accessories do not load the host 3.3 V rail. SHDN is tied to IN, so U4 runs whenever SYS_5V is up; SENSE is tied to OUT. C9 is the U4 input capacitor, C10 the output capacitor.
Notes
1. PI_5V: host 5 V from header pins 2 and 4 on sheet 1 (Host interface). 2. SYS_5V: eFuse-protected 5 V for U4, the motor supply and supervisor on sheet 3 (Motor isolation and current limits), the safety LDO and servo switch on sheet 4 (Independent safety supervisor), the LED driver and underlights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

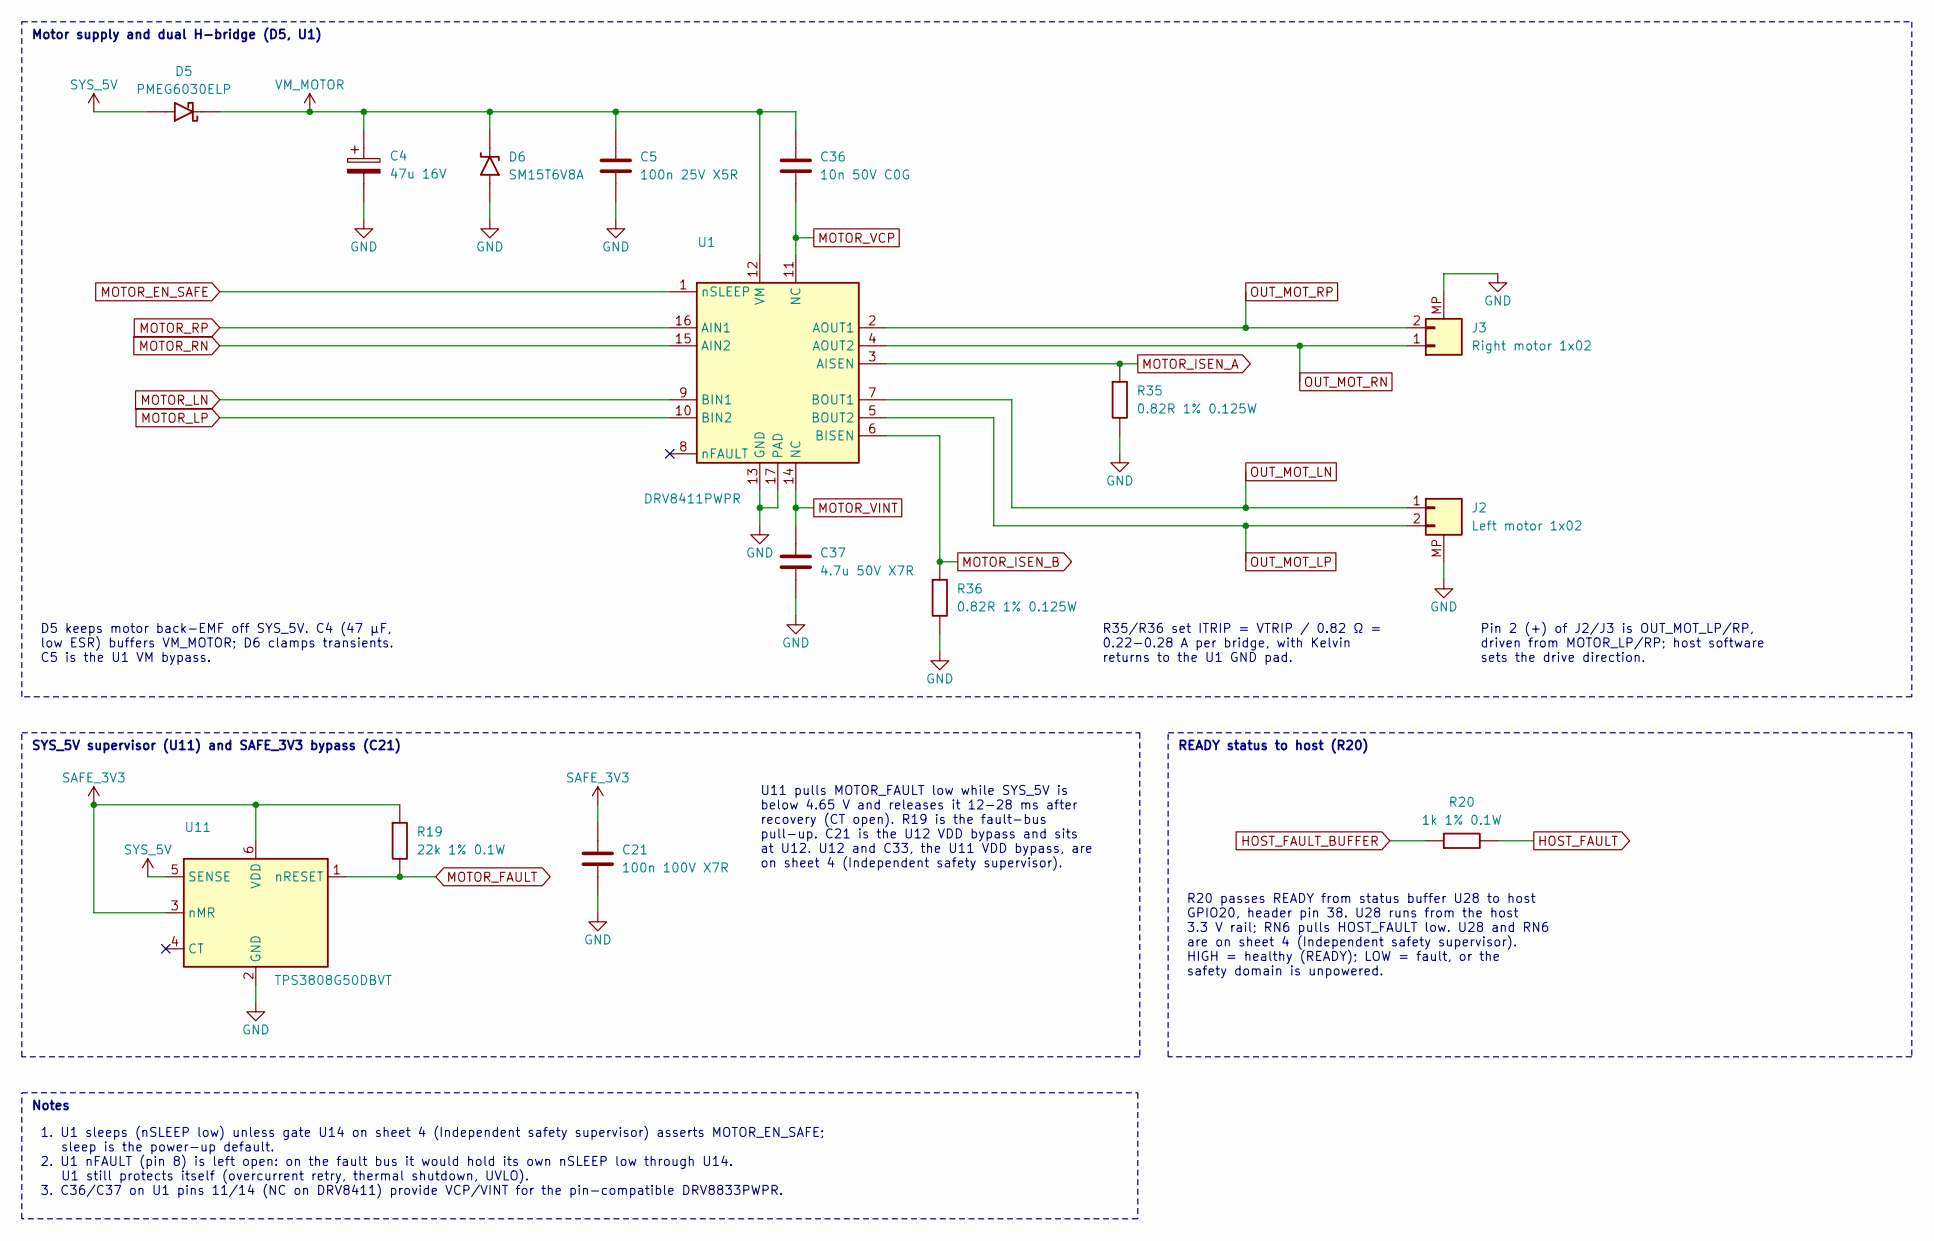
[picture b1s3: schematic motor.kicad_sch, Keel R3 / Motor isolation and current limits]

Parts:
C4: 47u 16V; CP_Elec_6.3x5.8; MPN EEE-FP1C470AP
C5: 100n 25V X5R; C_0201_0603Metric; MPN GRM033R61E104KE14D
C21: 100n 100V X7R; C_0603_1608Metric; MPN GRM188R72A104KA35D
C36: 10n 50V C0G; C_0603_1608Metric; MPN GRM1885C1H103JA01D
C37: 4.7u 50V X7R; C_1206_3216Metric; MPN GRM31CR71H475KA12L
D5: PMEG6030ELP; D_SOD-128; MPN PMEG6030ELP,115
D6: SM15T6V8A; D_SMC; MPN SM15T6V8A-TR
J2: Left motor 1x02; JST_ZH_S2B-ZR-SM4A-TF_1x02-1MP_P1.50mm_Horizontal; MPN S2B-ZR-SM4A-TF
J3: Right motor 1x02; JST_ZH_S2B-ZR-SM4A-TF_1x02-1MP_P1.50mm_Horizontal; MPN S2B-ZR-SM4A-TF
R19: 22k 1% 0.1W; R_0603_1608Metric; MPN RC0603FR-0722KL
R20: 1k 1% 0.1W; R_0603_1608Metric; MPN RC0603FR-071KL
R35, R36: 0.82R 1% 0.125W; R_0805_2012Metric; MPN RL0805FR-070R82L
U1: DRV8411PWPR; DRV8411A_PWP0016_C01_ExternalVias; MPN DRV8411PWPR
U11: TPS3808G50DBVT; SOT-23-6; MPN TPS3808G50DBVT

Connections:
GND: C4.2, C5.2, C21.2, C37.2, D6.2 (A), J2.MP (mounts), J3.MP (mounts), R35.2, R36.2, U1.13 (GND), U1.17 (THERMAL_PAD), U11.2 (GND); also elsewhere on the board
HOST_FAULT: R20.2; also elsewhere on the board
HOST_FAULT_BUFFER: R20.1; also elsewhere on the board
MOTOR_EN_SAFE: U1.1 (VREF); also elsewhere on the board
MOTOR_FAULT: R19.2, U11.1 (nRESET); also elsewhere on the board
MOTOR_ISEN_A: R35.1, U1.3 (PGNDA); also elsewhere on the board
MOTOR_ISEN_B: R36.1, U1.6 (PGNDB); also elsewhere on the board
MOTOR_LN: U1.9 (BIN1); also elsewhere on the board
MOTOR_LP: U1.10 (BIN2); also elsewhere on the board
MOTOR_RN: U1.15 (AIN2); also elsewhere on the board
MOTOR_RP: U1.16 (AIN1); also elsewhere on the board
MOTOR_VCP: C36.1, U1.11 (BIPROPI)
MOTOR_VINT: C37.1, U1.14 (AIPROPI)
OUT_MOT_LN: J2.1, U1.7 (BOUT1)
OUT_MOT_LP: J2.2, U1.5 (BOUT2)
OUT_MOT_RN: J3.1, U1.4 (AOUT2)
OUT_MOT_RP: J3.2, U1.2 (AOUT1)
SAFE_3V3: C21.1, R19.1, U11.3 (nMR), U11.6 (VDD); also elsewhere on the board
SYS_5V: D5.2 (A), U11.5 (SENSE); also elsewhere on the board
VM_MOTOR: C4.1, C5.1, C36.2, D5.1 (K), D6.1 (K), U1.12 (VM); also elsewhere on the board

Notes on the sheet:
Motor supply and dual H-bridge (D5, U1)
D5 keeps motor back-EMF off SYS_5V. C4 (47 µF, low ESR) buffers VM_MOTOR; D6 clamps transients. C5 is the U1 VM bypass.
R35/R36 set ITRIP = VTRIP / 0.82 Ω = 0.22-0.28 A per bridge, with Kelvin returns to the U1 GND pad.
Pin 2 (+) of J2/J3 is OUT_MOT_LP/RP, driven from MOTOR_LP/RP; host software sets the drive direction.
SYS_5V supervisor (U11) and SAFE_3V3 bypass (C21)
U11 pulls MOTOR_FAULT low while SYS_5V is below 4.65 V and releases it 12-28 ms after recovery (CT open). R19 is the fault-bus pull-up. C21 is the U12 VDD bypass and sits at U12. U12 and C33, the U11 VDD bypass, are on sheet 4 (Independent safety supervisor).
READY status to host (R20)
R20 passes READY from status buffer U28 to host GPIO20, header pin 38. U28 runs from the host 3.3 V rail; RN6 pulls HOST_FAULT low. U28 and RN6 are on sheet 4 (Independent safety supervisor). HIGH = healthy (READY); LOW = fault, or the safety domain is unpowered.
Notes
1. U1 sleeps (nSLEEP low) unless gate U14 on sheet 4 (Independent safety supervisor) asserts MOTOR_EN_SAFE; sleep is the power-up default. 2. U1 nFAULT (pin 8) is left open: on the fault bus it would hold its own nSLEEP low through U14. U1 still protects itself (overcurrent retry, thermal shutdown,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

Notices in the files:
software/libkeel/src/backend/sim/sim_board.c:
SPDX-License-Identifier: MIT
README.md:
Licences:
Part | Licence | Text
Hardware design: `hardware/` (KiCad project and project-made libraries, production files, 3D model, renders, documentation) | CERN-OHL-P-2.0 | [`LICENSE-HARDWARE`](LICENSE-HARDWARE)
Robot chassis: `chassis/` (print files, assembled model, build guide, renders) | CERN-OHL-P-2.0 | [`LICENSE-HARDWARE`](LICENSE-HARDWARE)
Firmware: project files in `firmware/safety-mcu/` | MIT | [`LICENSE`](LICENSE)
Software: `software/libkeel/`, `software/bindings/` | MIT | [`LICENSE`](LICENSE)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
